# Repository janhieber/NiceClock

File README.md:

# About
This project was started for testing the new KiCad v4
as a replacement for EAGLE.

I want a free ECAD software without the limiations, so
I started this to explore the capabilities of KiCad.

Conclusion: KiCad can be a good replacement for EAGLE and co.  
It has some rough edges, but makes a point with some
great features.

# Nice 3D pics :)

# Current progress
### Hardware

TODO:  
- [ ] schematic
  - [x] LEDs and WS2803 ICs
    - [x] wire up
    - [x] connect to CPU
  - [x] CPU (STM32F1)
  - [ ] real time clock
    - [x] wire up
    - [x] connect to CPU
  - [x] SWD program and serial terminal
- [ ] layout
  - [ ] LEDs
  - [ ] WS2803
  - [ ] STM32 CPU
  - [x] RTC
  - [x] power supply

For the current progress, look at the
[schematic](https://raw.githubusercontent.com/janhieber/NiceClock/master/hardware/doc/schematic.pdf)
and
[layout](https://raw.githubusercontent.com/janhieber/NiceClock/master/hardware/doc/board.pdf) PDFs.

### Software
Software development not started yes.

The software will be written in pure C.  
STM32CubeMX will be used as initialisation code generator.

TODO:  
- [ ] STM32 software
  - [ ] hardware initialisation
  - [ ] cooperative scheduler
  - [ ] real time clock code
  - [ ] LED control code for WS2803 ICs via SPI
  - [ ] DCF77 code
  - [ ] Bootloader for serial program download over UART
- [ ] Software to flash firmware via serial connection

# Community
If you are interessted in this, feel free to contact me.  
I'll also have some spare PCBs when I ordner them, so I'll sell them.

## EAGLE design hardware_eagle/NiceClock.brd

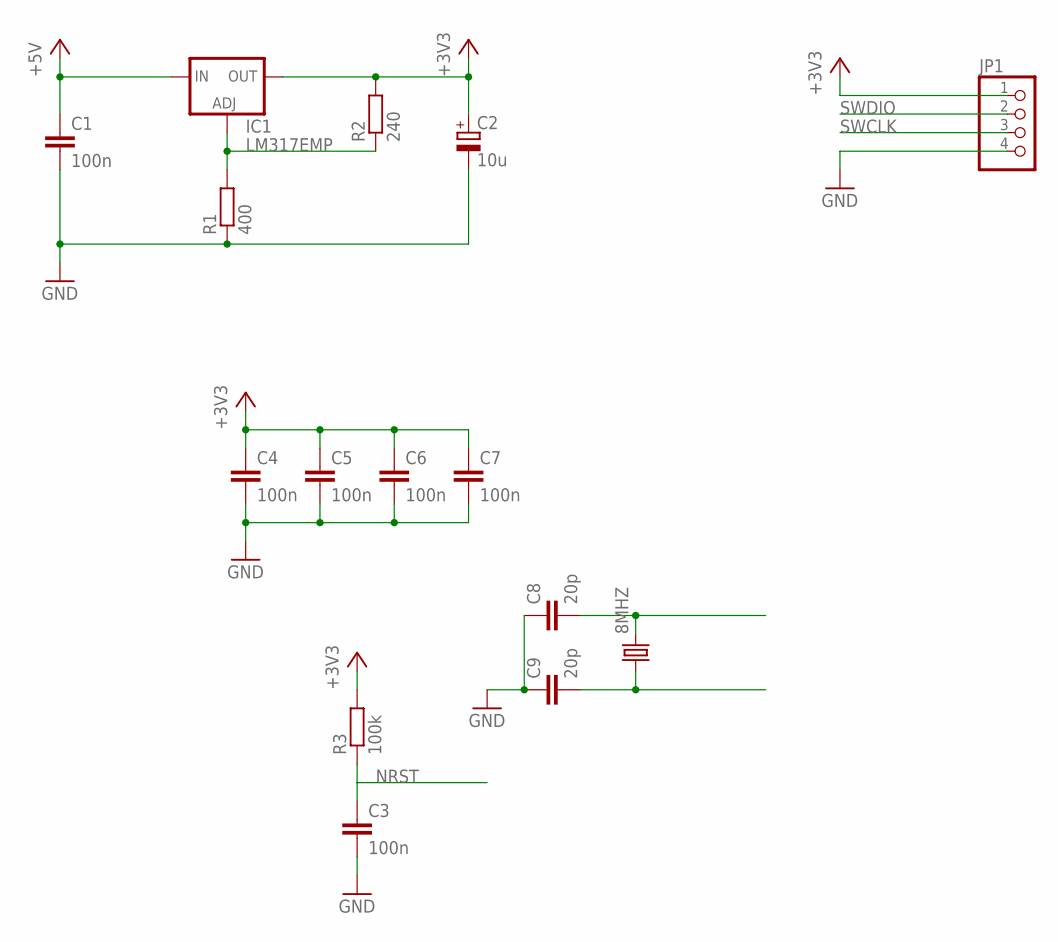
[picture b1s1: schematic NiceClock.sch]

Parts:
8MHZ: CRYSTALHC49UP; HC49UP
C1, C3, C4, C5, C6, C7: 100n; C0603
C2: 10u; C/6032-28W
C8, C9: 20p; C0603
IC1: LM317EMP; SOT223
JP1: PINHD-1X4/90; 1X04/90
R1: 400; R0603
R2: 240; R0603
R3: 100k; R0603

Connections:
+3V3: C2.+, C4.1, C5.1, C6.1, C7.1, IC1.4 (OUT), JP1.1, R2.2, R3.2
+5V: C1.1, IC1.3 (IN)
GND: C1.2, C2.-, C3.2, C4.2, C5.2, C6.2, C7.2, C8.1, C9.1, JP1.4, R1.1
unnamed: IC1.1 (ADJ), R1.2, R2.1
unnamed: 8MHZ.1, C9.2
unnamed: 8MHZ.2, C8.2
NRST: C3.1, R3.1
SWCLK: JP1.3
SWDIO: JP1.2

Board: 2 copper layers, 15 parts (0 on the bottom side), 7 nets, no tracks yet.

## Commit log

2015-12-07 initial design stuff
2015-12-07 kicad changes + new eagle schematic
2015-12-18 kicad updates
2015-12-25 reworked schematic + new board
2015-12-25 placed LEDs and other stuff
2015-12-26 some tracks and 3D drawing
2015-12-27 pcb updates
2015-12-27 update docu stuff
2015-12-27 use relative path to 3D models
2015-12-28 added switches, DC jack + some routing
2015-12-30 some updates
